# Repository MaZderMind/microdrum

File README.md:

# MicroDrum - Ein Mikrocontroller-Basierter Drum-Computer
Dies ist das Sourcecode-Repo des [Microdum-Projektes](http://microdrum.wordpress.com/). Die Hardware-Spezifikationen und Software-Komponenten werden hier veröffentlicht, Hintergründe und Geschichte können im [Blog](http://microdrum.wordpress.com/) nachgelesen werden.

## Kontakt
Wenn du Fragen hast, melde dich bei microdrum@mazdermind.de oder benutze das Github-Nachrichten-System

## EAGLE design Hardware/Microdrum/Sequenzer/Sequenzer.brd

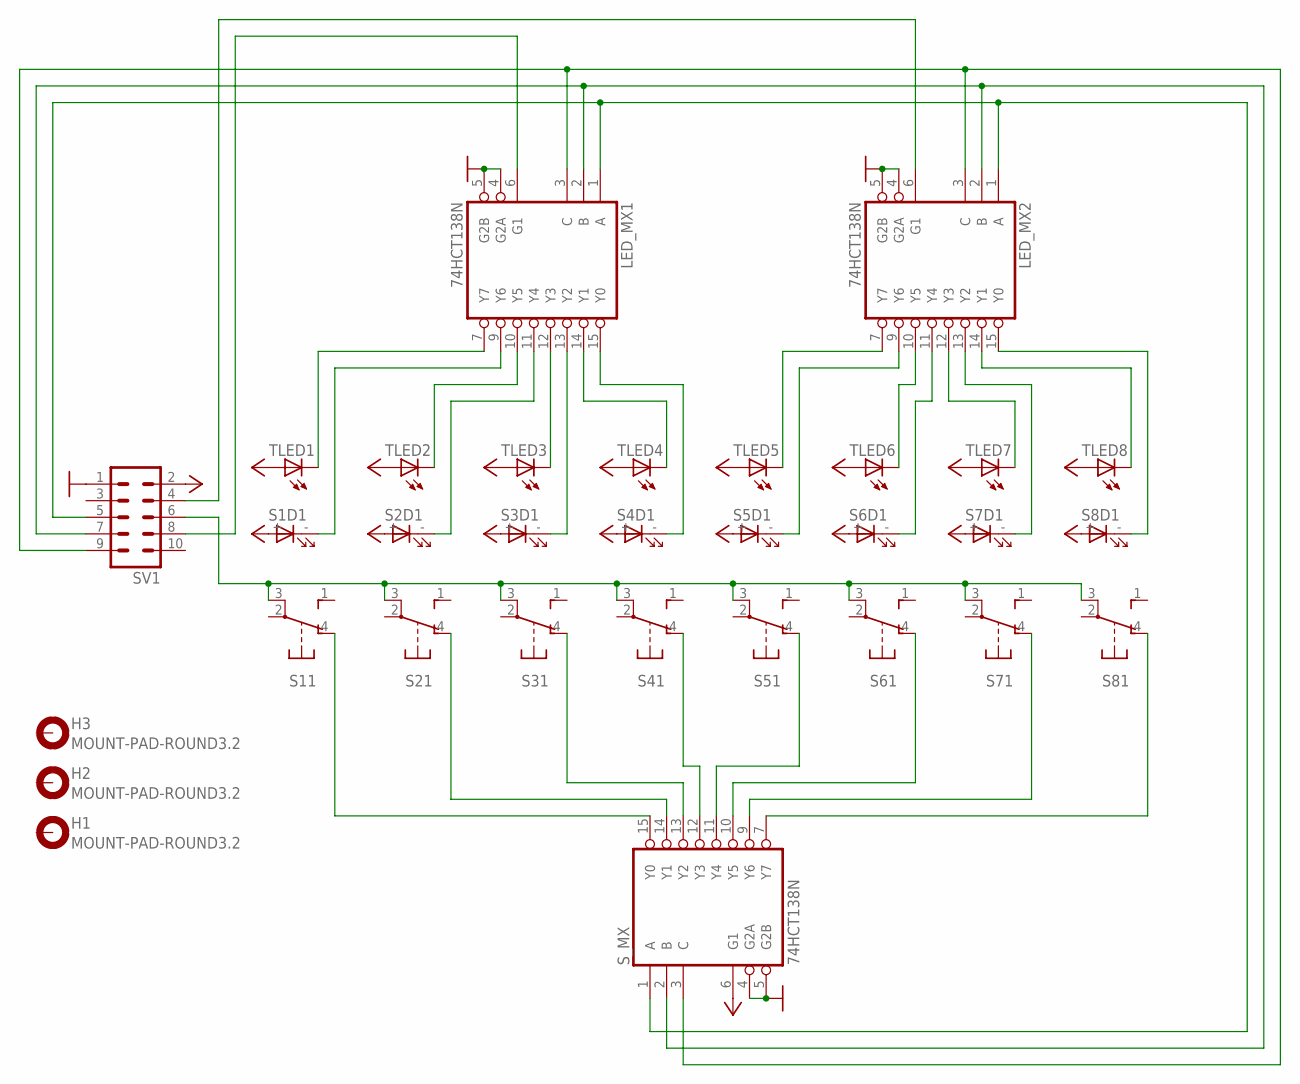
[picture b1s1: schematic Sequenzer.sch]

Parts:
H1, H2, H3: MOUNT-PAD-ROUND3.2; 3,2-PAD
LED_MX1, LED_MX2: 74HCT138N; DIL16
S1, S2, S3, S4, S5, S6, S7, S8: SRKL
SV1: ML10
S_MX: 74HCT138N; DIL16
TLED1, TLED2, TLED3, TLED4, TLED5, TLED6, TLED7, TLED8: LED3MM

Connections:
1: LED_MX1.1 (A), LED_MX2.1 (A), SV1.5, S_MX.1 (A)
2: LED_MX1.2 (B), LED_MX2.2 (B), SV1.7, S_MX.2 (B)
3: LED_MX1.3 (C), LED_MX2.3 (C), SV1.9, S_MX.3 (C)
GND: LED_MX1.4 (G2A), LED_MX1.5 (G2B), LED_MX1.8 (GND), LED_MX2.4 (G2A), LED_MX2.5 (G2B), LED_MX2.8 (GND), SV1.1, S_MX.4 (G2A), S_MX.5 (G2B), S_MX.8 (GND)
MX1EN: LED_MX1.6 (G1), SV1.8
MX2EN: LED_MX2.6 (G1), SV1.4
unnamed: S8.4 (O), S_MX.7 (Y7)
unnamed: S7.4 (O), S_MX.9 (Y6)
unnamed: S6.4 (O), S_MX.10 (Y5)
unnamed: S5.4 (O), S_MX.11 (Y4)
unnamed: S4.4 (O), S_MX.12 (Y3)
unnamed: S3.4 (O), S_MX.13 (Y2)
unnamed: S2.4 (O), S_MX.14 (Y1)
unnamed: S1.4 (O), S_MX.15 (Y0)
SLED: LED_MX1.13 (Y2), S3.- (C)
SLED1: LED_MX1.9 (Y6), S1.- (C)
SLED2: LED_MX1.11 (Y4), S2.- (C)
SLED4: LED_MX1.15 (Y0), S4.- (C)
SLED5: LED_MX2.9 (Y6), S5.- (C)
SLED6: LED_MX2.11 (Y4), S6.- (C)
SLED7: LED_MX2.13 (Y2), S7.- (C)
SLED8: LED_MX2.15 (Y0), S8.- (C)
S_SENSE: S1.3, S2.3, S3.3, S4.3, S5.3, S6.3, S7.3, S8.3, SV1.6
TLED1: LED_MX1.7 (Y7), TLED1.K (C)
TLED2: LED_MX1.10 (Y5), TLED2.K (C)
TLED3: LED_MX1.12 (Y3), TLED3.K (C)
TLED4: LED_MX1.14 (Y1), TLED4.K (C)
TLED5: LED_MX2.7 (Y7), TLED5.K (C)
TLED6: LED_MX2.10 (Y5), TLED6.K (C)
TLED7: LED_MX2.12 (Y3), TLED7.K (C)
TLED8: LED_MX2.14 (Y1), TLED8.K (C)
VCC: LED_MX1.16 (VCC), LED_MX2.16 (VCC), S1.+ (A), S2.+ (A), S3.+ (A), S4.+ (A), S5.+ (A), S6.+ (A), S7.+ (A), S8.+ (A), SV1.2, S_MX.6 (G1), S_MX.16 (VCC), TLED1.A, TLED2.A, TLED3.A, TLED4.A, TLED5.A, TLED6.A, TLED7.A, TLED8.A

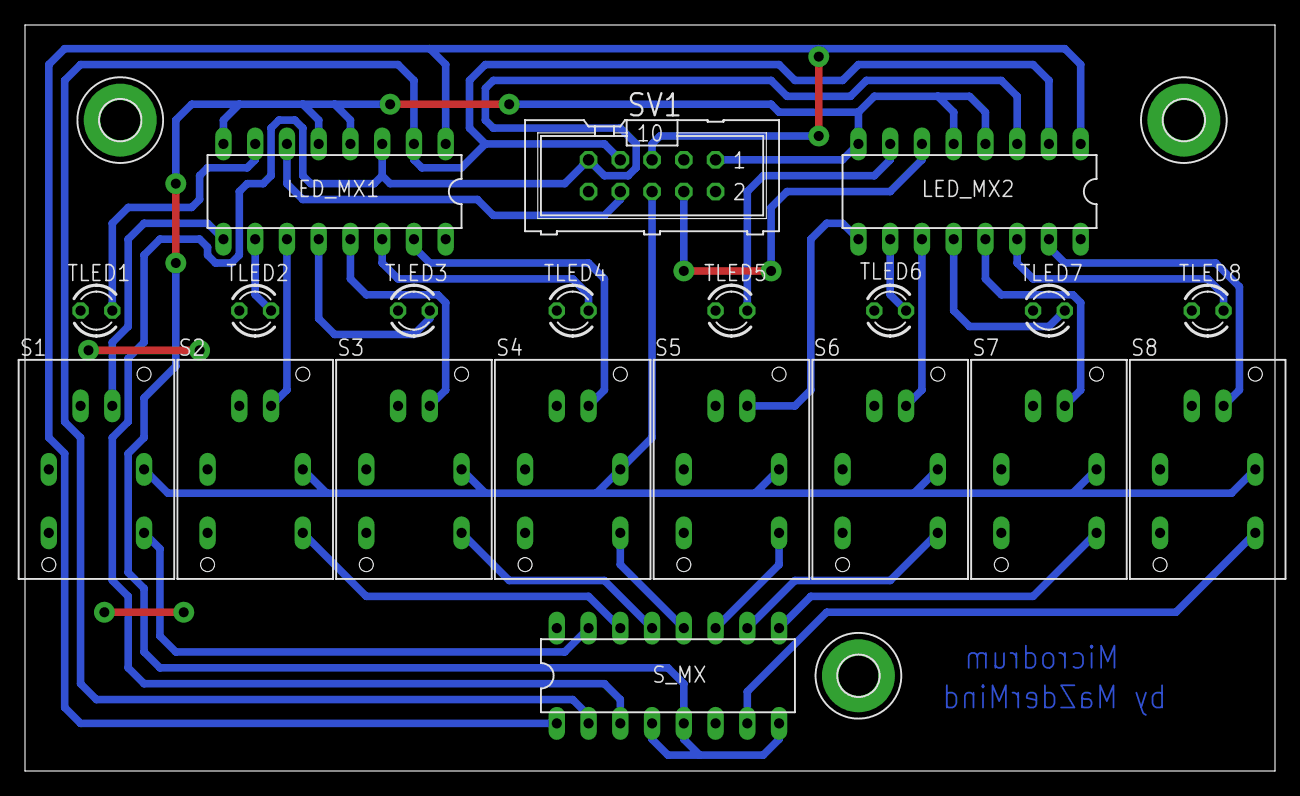
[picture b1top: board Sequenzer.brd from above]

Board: 2 copper layers, 100.0 x 59.7 mm, 23 parts (0 on the bottom side), 32 nets.

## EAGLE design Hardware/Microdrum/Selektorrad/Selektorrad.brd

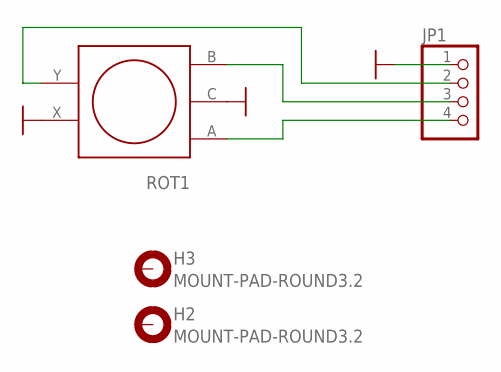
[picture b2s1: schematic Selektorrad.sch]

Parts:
H2, H3: MOUNT-PAD-ROUND3.2; 3,2-PAD
JP1: PINHD-1X4; 1X04
ROT1: STEC12E08; EC12E24244

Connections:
GND: JP1.1, ROT1.C, ROT1.X
unnamed: JP1.3, ROT1.B
unnamed: JP1.4, ROT1.A
unnamed: JP1.2, ROT1.Y

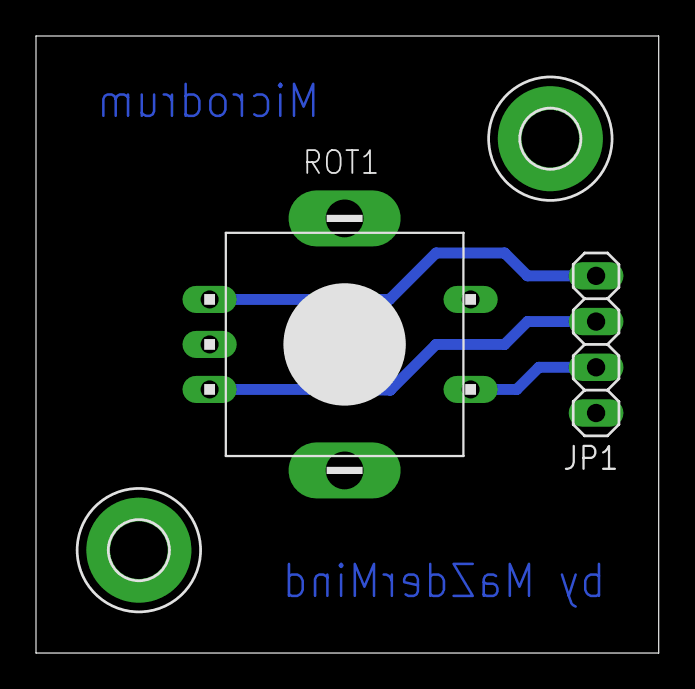
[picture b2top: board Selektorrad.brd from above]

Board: 2 copper layers, 34.6 x 34.3 mm, 4 parts (0 on the bottom side), 4 nets.

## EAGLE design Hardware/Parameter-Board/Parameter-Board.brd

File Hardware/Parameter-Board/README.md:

# MicroDrum - Parameter-Board
Dieser Ordner enthält Schemazeichnung und Platinenlayouts für die Parameter-Boards. Ein solches Board ist mit je 16 Drehpotentiometern bestückt und bietet dem Nutzer die Möglichkeit, die Klang-Parameter der einzelnen Instrumente zu konfigurieren.

## Aufbau
Damit der Atmel so viele analoge Signale (8×4 = 32) überhaupt verarbeiten kann, kommen [74HC4051](http://www.datasheetcatalog.org/datasheet/philips/74HC4051.pdf) 8-Kanal Analog Multiplexer/Demultiplexer zum Einsatz. Bei diesen Bauteilen wird mit 3 digitalen Leitungen einer der 8 Eingangspins gewählt, welcher dann mit dem Ausgangsport verbunden wird.

Wir verwenden 4 solcher ICs, deren Auswahlports jeweils verbunden sind, um mit 3 digitalen und 4 analogen Eingängen an der MCU alle 32 Potis messen zu können. Dazu werden zwei dieser Platinen benötigt, die je 16 Potis und 2 Multiplexer beinhalten.

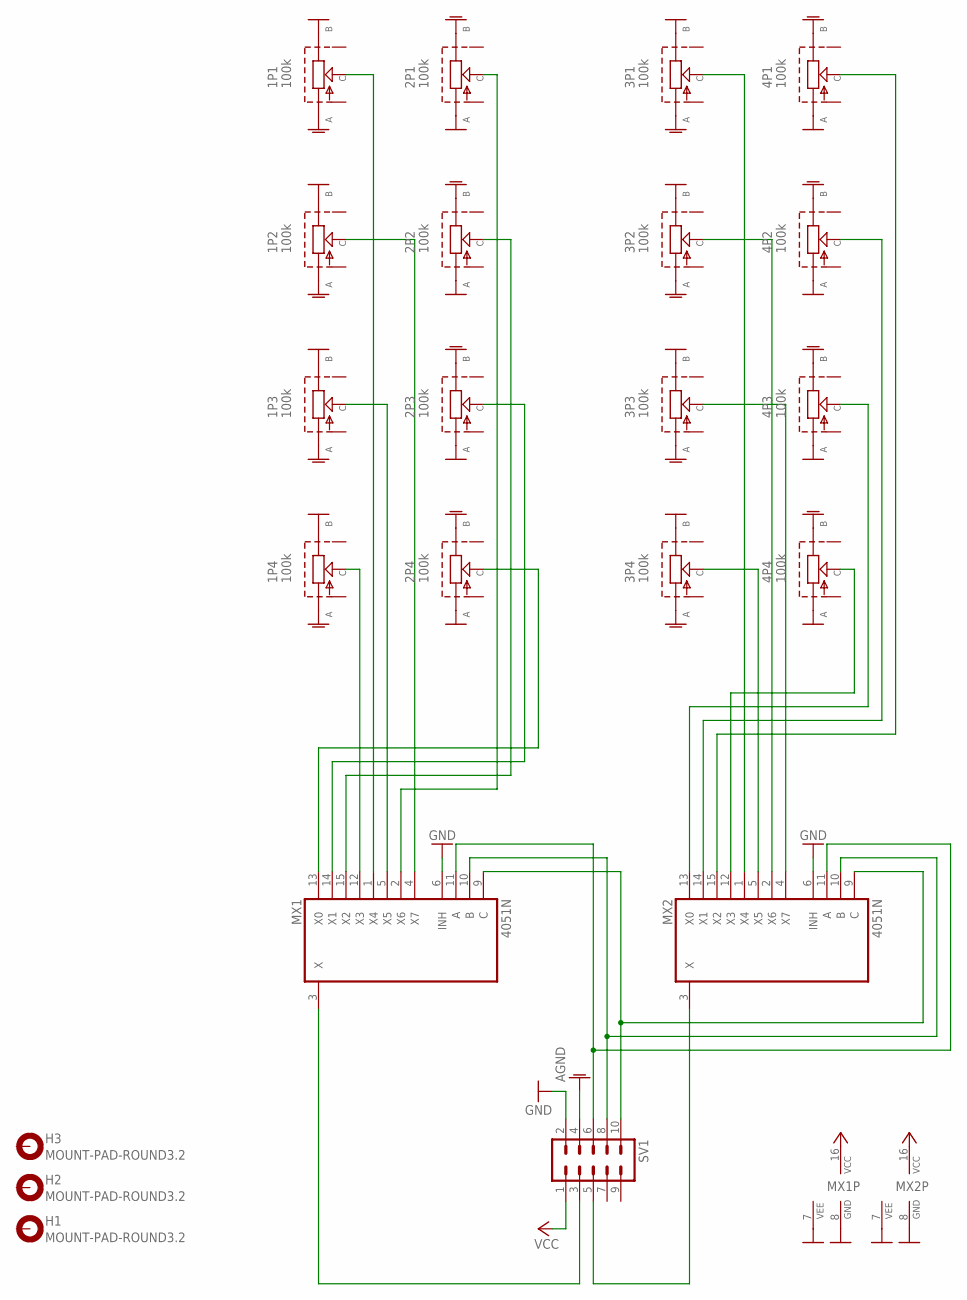
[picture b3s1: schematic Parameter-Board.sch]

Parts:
1P1, 1P2, 1P3, 1P4, 2P1, 2P2, 2P3, 2P4, 3P1, 3P2, 3P3, 3P4, 4P1, 4P2, 4P3, 4P4: 100k; RK09K113
H1, H2, H3: MOUNT-PAD-ROUND3.2; 3,2-PAD
MX1, MX2: 4051N; DIL16
SV1: ML10

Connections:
0MX1: 2P4.C, MX1.13 (X0)
0MX2: 4P3.C, MX2.13 (X0)
1MX1: 2P3.C, MX1.14 (X1)
1MX2: 4P2.C, MX2.14 (X1)
2MX1: 2P2.C, MX1.15 (X2)
2MX2: 4P1.C, MX2.15 (X2)
3MX1: 1P4.C, MX1.12 (X3)
3MX2: 4P4.C, MX2.12 (X3)
4MX1: 1P1.C, MX1.1 (X4)
4MX2: 3P1.C, MX2.1 (X4)
5MX1: 1P3.C, MX1.5 (X5)
5MX2: 3P4.C, MX2.5 (X5)
6MX1: 2P1.C, MX1.2 (X6)
6MX2: 3P2.C, MX2.2 (X6)
7MX1: 1P2.C, MX1.4 (X7)
7MX2: 3P3.C, MX2.4 (X7)
A: MX1.11 (A), MX2.11 (A), SV1.6
AGND: 1P1.A, 1P2.A, 1P3.A, 1P4.A, 2P1.B, 2P2.B, 2P3.B, 2P4.B, 3P1.A, 3P2.A, 3P3.A, 3P4.A, 4P1.B, 4P2.B, 4P3.B, 4P4.B, SV1.4
B: MX1.10 (B), MX2.10 (B), SV1.8
C: MX1.9 (C), MX2.9 (C), SV1.10
GND: 1P1.B, 1P2.B, 1P3.B, 1P4.B, 2P1.A, 2P2.A, 2P3.A, 2P4.A, 3P1.B, 3P2.B, 3P3.B, 3P4.B, 4P1.A, 4P2.A, 4P3.A, 4P4.A, MX1.6 (INH), MX1.7 (VEE), MX1.8 (GND), MX2.6 (INH), MX2.7 (VEE), MX2.8 (GND), SV1.2
VCC: MX1.16 (VCC), MX2.16 (VCC), SV1.1
X1: MX1.3 (X), SV1.3
X2: MX2.3 (X), SV1.5

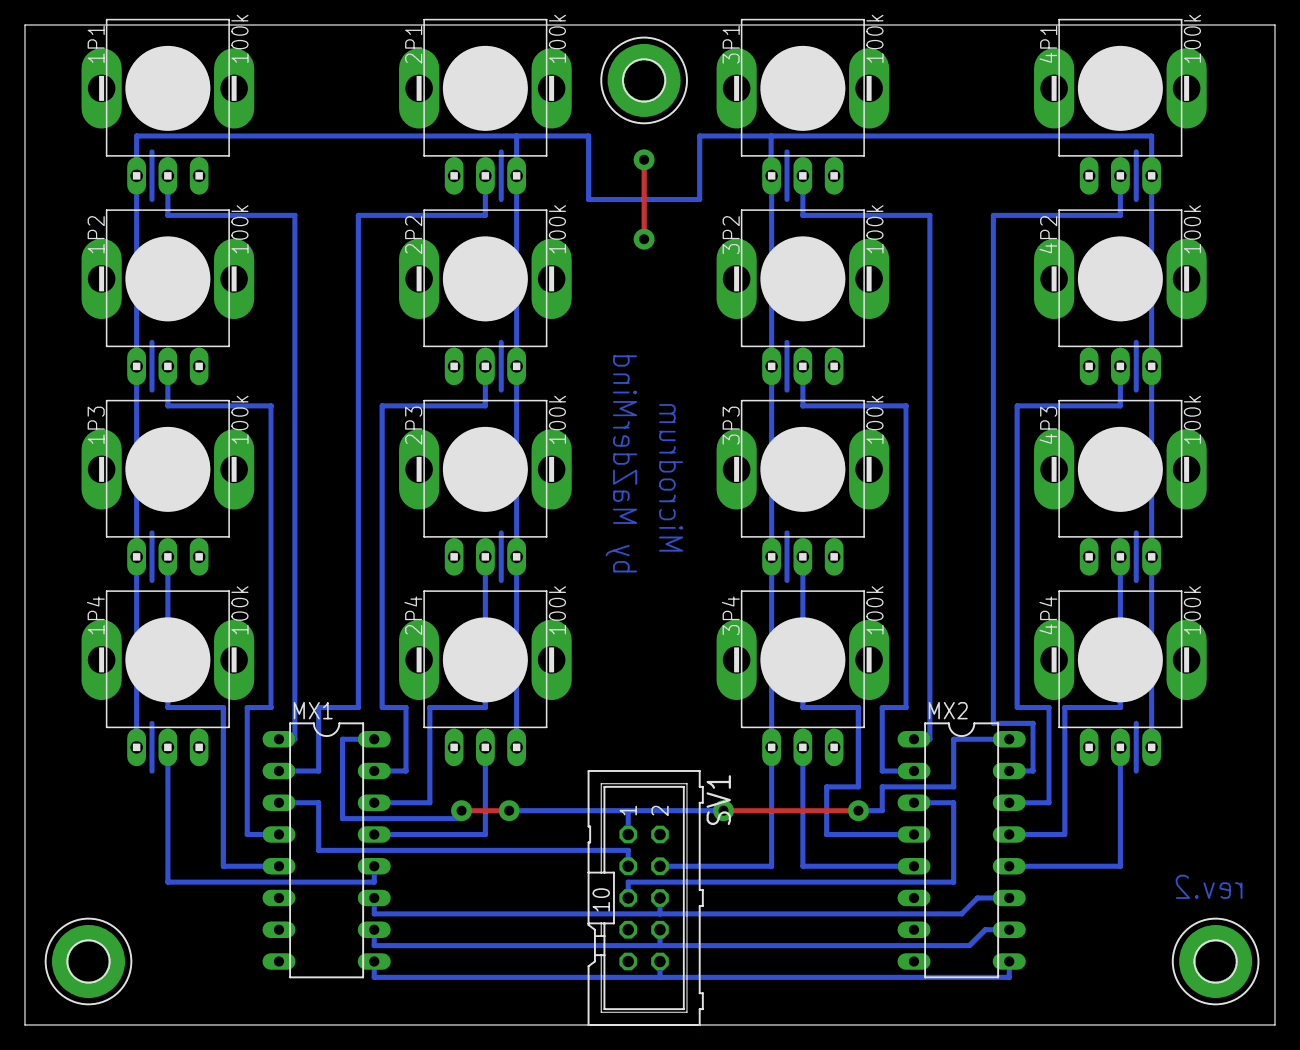
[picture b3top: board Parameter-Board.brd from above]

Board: 2 copper layers, 100.0 x 80.0 mm, 22 parts (0 on the bottom side), 24 nets.

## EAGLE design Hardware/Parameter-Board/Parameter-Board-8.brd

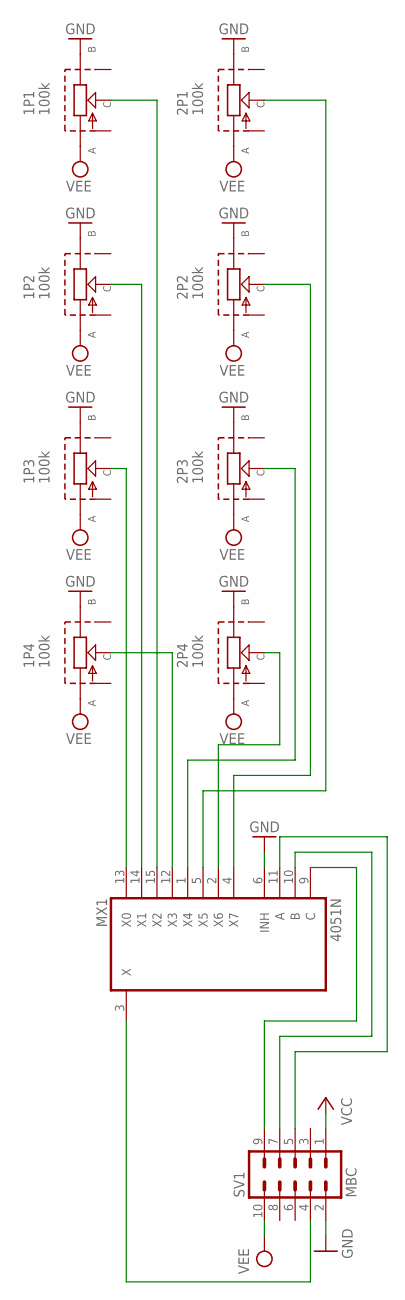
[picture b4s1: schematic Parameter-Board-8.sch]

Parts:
1P1, 1P2, 1P3, 1P4, 2P1, 2P2, 2P3, 2P4: 100k; RK09K113
MX1: 4051N; DIL16
SV1: MBC; ML10

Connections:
1P1: 1P1.C, MX1.15 (X2)
1P2: 1P2.C, MX1.14 (X1)
1P3: 1P3.C, MX1.13 (X0)
1P4: 1P4.C, MX1.12 (X3)
2P1: 2P1.C, MX1.5 (X5)
2P2: 2P2.C, MX1.4 (X7)
2P3: 2P3.C, MX1.1 (X4)
2P4: 2P4.C, MX1.2 (X6)
A: MX1.11 (A), SV1.5
B: MX1.10 (B), SV1.7
C: MX1.9 (C), SV1.9
GND: 1P1.B, 1P2.B, 1P3.B, 1P4.B, 2P1.B, 2P2.B, 2P3.B, 2P4.B, MX1.6 (INH), MX1.8 (GND), SV1.2
VCC: MX1.16 (VCC), SV1.1
VEE: 1P1.A, 1P2.A, 1P3.A, 1P4.A, 2P1.A, 2P2.A, 2P3.A, 2P4.A, MX1.7 (VEE), SV1.10
Z: MX1.3 (X), SV1.4

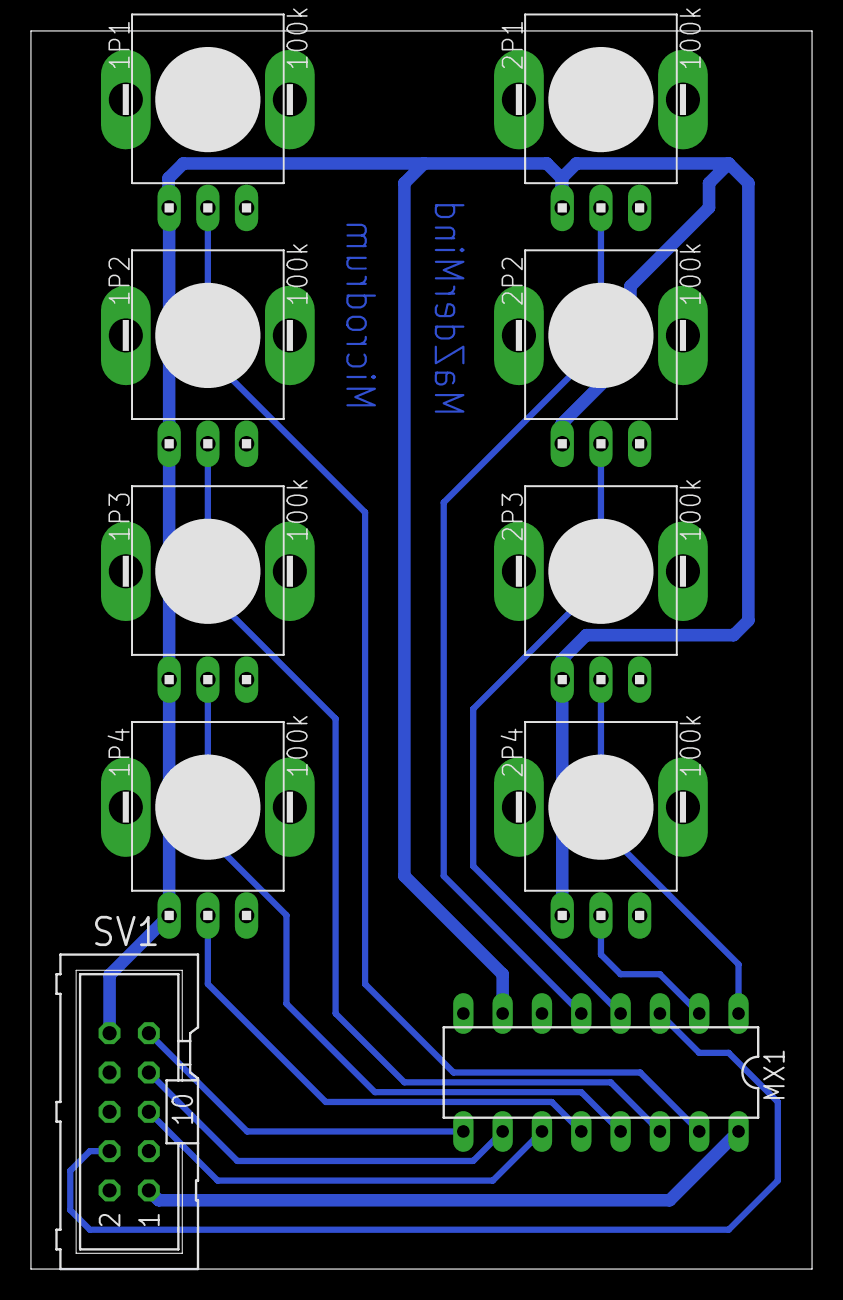
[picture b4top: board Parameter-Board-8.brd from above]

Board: 2 copper layers, 50.5 x 80.0 mm, 10 parts (0 on the bottom side), 15 nets.

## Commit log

2012-01-17 markdown ftw!
2012-01-17 Quelldatei für die Grafik überden Anschluss der Midi-zu-Usb-Brücke
2012-01-17 Dokumentation zum "Midi-zu-Usb"-Ordner
2012-01-17 Layout und Schematik eines Parameter-Boards mit 8 Potis
2012-01-17 Eagle Backup-Dateien ignorieren
2012-01-17 Textebenen hinzufügen
2012-01-17 Verweis auf ein Datasheet mit Darstellung der PDIP-Gehäuseform ändern
2012-01-19 move board to the left and make it smaller
2012-01-19 move text and add restrict-polygons
2012-01-19 Board-Layout und Schematik mit 16 Potentiometern und 2 Multiplex-ICs
2012-01-19 VEE ist die negative Referenzspannung, welche in unserem Fall GND ist. Die Referenz-Voltage des MCU ist hingegen mit AGND verbunden.
2012-01-19 fix clearance problem
2012-01-21 Das komplette Board wurde neu geroutet, so dass keine Top-Layer-Brücke nötig und die Leiterbahnführung einheitlicher ist
2012-01-21 altes Board mit 8 Potis löschen
2012-01-21 Das Mounthole wurde zwischen den Potentiometern zentriert
2012-01-22 Test-Programm zum ansteuern des LCDs und der Midi-Brücke
2012-01-22 remove wrong instrument names
2012-01-22 fix typo in comment
2012-01-23 Whitespacenazi!
2012-01-23 fix utf8 problems
2012-01-28 .atsuo-Datei (?) löschen
2012-01-28 Readme-Datei hinzufügen
2012-01-28 Who? Wo war die Datei denn hin?
2012-01-28 zweite Midi-Demo, welche die Midi-Clock des Host-Computers benutzt, um die generieten Noten zu steuern
2012-02-18 Sourcecode und Schaltplan für Laminator-Temperaturregelung
2012-03-06 Endgültiges Boardlayout
2012-03-06 Information zu Revision
2012-03-08 Wenn die drei Bahnenden den gleichen Winkel haben, schaut's einfach schöner aus
2012-03-08 einfacher Schaltplan zur Beschreibung der Belichterplatinen
2012-03-15 Testdatei für Belichtungsreihe
2012-03-26 Ordnerstruktur aufgeräumt, damit besser zwischen den Platinen und Schemata des Projektes und denen im weiteren Umfeld der Herstellung angefertigten unterschieden werden kann.
2012-03-28 Testprogramm für das Parameter-Board
2012-04-12 minimized selector board
2012-04-18 Prototyp der Sequenzer Platine
2012-04-18 Parameter-Board umbenennen
2012-04-18 Leichte veränderungen in Routing und Positionierung
2012-04-19 Langsam nimmt es Form an
2012-04-21 Vorläufig fertiges Layout
2012-04-21 Leicht geänderte Routenführung
2012-04-21 Width wieder zurückgeändert, Dimension begradigt
2012-04-21 Layer-Sichtbarkeit auf Standard
2012-04-21 Label-Placement
2012-04-21 Label-Placement im Schaltplan
2012-04-21 Route aus optischen Gründen geändert
2012-04-23 Basisdateien für Demo-Firmware diesmal mit Linux-Toolchain (Makefiles und passender gitignore)
2012-04-23 Bohrlöcher
2012-04-23 Speicheradressen für 4x20 Zeichen-Display angepasst
2012-04-25 Basis des späteren Firmware-Frameworks
2012-04-25 Programmgröße bei 'make program' anzeigen, weitere optimierungen
2012-04-25 I/O-Code aufräumen, Selektorrad abfragen und Instrumentenname anzeigen
2012-04-25 Makefile-Target um Leerzeichen am Ende von Zeilen zu entfernen
2012-04-25 IO-Komponente für die Parameter-Boards aus dem entsprechenden Testcase
2012-04-26 Entprellen des Drehrads, umstellen auf Post-Select Post-SElect beudeutet, dass erst nach abschließen eines Schrittes des Drehrads gezählt wird, nicht gleich zu Beginn
2012-04-26 fix missing spaces
2012-04-26 Zu Unix-Zeilenende wandeln
2012-04-28 Midi einbindung, leider noch desync
2012-04-28 Endlich synchron und mit Song Position Pointer support
2012-04-29 Aufräumen des Clocking-Codes nach den Ergebnissen des Hack-Weekends verbessern der Synchronizität durch berechnen der Beat-Zahl aus dem Midi-Clock-Count Gegensteuern gegen Probleme mit zu kurzen Noten
2012-05-01 Reparieren und Optimieren der Clock-Routinen
2012-05-01 Besseres Instrumenten-Triggering und Clearing
2012-05-01 Dokumentation
2012-05-01 Zu UTF8 wandeln
2012-05-06 Abhängigkeiten für Doku
2012-05-06 Dokumentation der Hauptdatei
2012-05-06 Hauptseite der Dokumentation
2012-05-06 definition auf 16 Taktschritte geändert
2012-05-06 io-config-Datei umbenannt
2012-05-06 Leerzeichen sind wichtig ;)
2012-05-06 Clean löscht auch die Dokumentation
2012-05-06 Umsortieren
2012-05-06 Kommentare um die Includes entfernen
2012-05-06 Dokumentation des Midi-Moduls
2012-05-06 die Bit-Helper-Macros benutzen
2012-05-06 Dokumentation der Bithelper-Makros
2012-05-06 Instrumentennamen dokumentiert
2012-05-06 Dokumentation des allgemeinen IO-Moduls
2012-05-06 Groß/Kleinschreibung
2012-05-06 Dokumentation der Selektorrad-Routinen
2012-05-06 Aufräumen der Dokumentation der LCD-Routinen für Doxygen
2012-05-06 Dokumentation der io_config-Datei
2012-05-06 Parameter-Routinen dokumentieren
2012-08-27 fix instrument overflow
2012-08-27 adopt to newer libc
2012-08-27 enable parameter boards in test-setup
2012-08-27 fix parameter boards in test-setup
2012-08-27 move selector detection into the cycle-loop in order to avoid missing selector ticks
2012-09-01 reduce memory footprint by splitting bits
2012-09-02 fix midi - argh\!
2012-09-02 use configurable midi channel
2012-09-02 versuch, das flattern zu minimieren
2012-09-02 io-parameter als midi-cc nachrichten übermitteln
2012-09-12 adapt to newer dox version
2012-09-12 only fetch the adc once, it's well - a little simpler
2012-09-12 reduce the number of shifts
2012-09-12 adress both boards
2012-09-23 reordr code
2012-09-23 thresholding
2012-09-23 spaces
2012-09-26 Eine Messung reicht
2012-09-26 Toggle Macros
2012-09-26 save another set of bytes
2012-09-26 PD2 wird verwendet, um die Geschwindigkeit des Sync-Loops zu visualisieren
2012-09-26 Testen der Sequencer-LEDs
2012-09-30 Sauberes implementieren der Sync-Led
2012-09-30 initialize the hardware first
2012-09-30 parameter-state-management in die parameter-lib verlagern und auf events umstricken
2012-09-30 readchip-Funktion vereinfachen
2012-09-30 Pedantischen GCC-Kompiler anschalten
2012-09-30 Pedantik- und Rechtschreib-Fehler beheben
2012-09-30 unbenutzte includes entfernen
2012-10-06 Schönere Umbrüche
2012-10-06 Doxygen die setbaud-Makros beibringen
2012-10-06 Sequenzer ansteuern
2012-10-07 move volatile variables into a struct
2012-10-07 Hex-Ausgabe-Methode
2012-10-07 Fehlender Include
2012-10-07 Fehlende Deklaration
2012-10-07 anpassen des presync-aufrufs
2012-10-07 Song-Position-Pointer support (does not yet work while clocks are coming in)
2013-08-21 store selected instruments
